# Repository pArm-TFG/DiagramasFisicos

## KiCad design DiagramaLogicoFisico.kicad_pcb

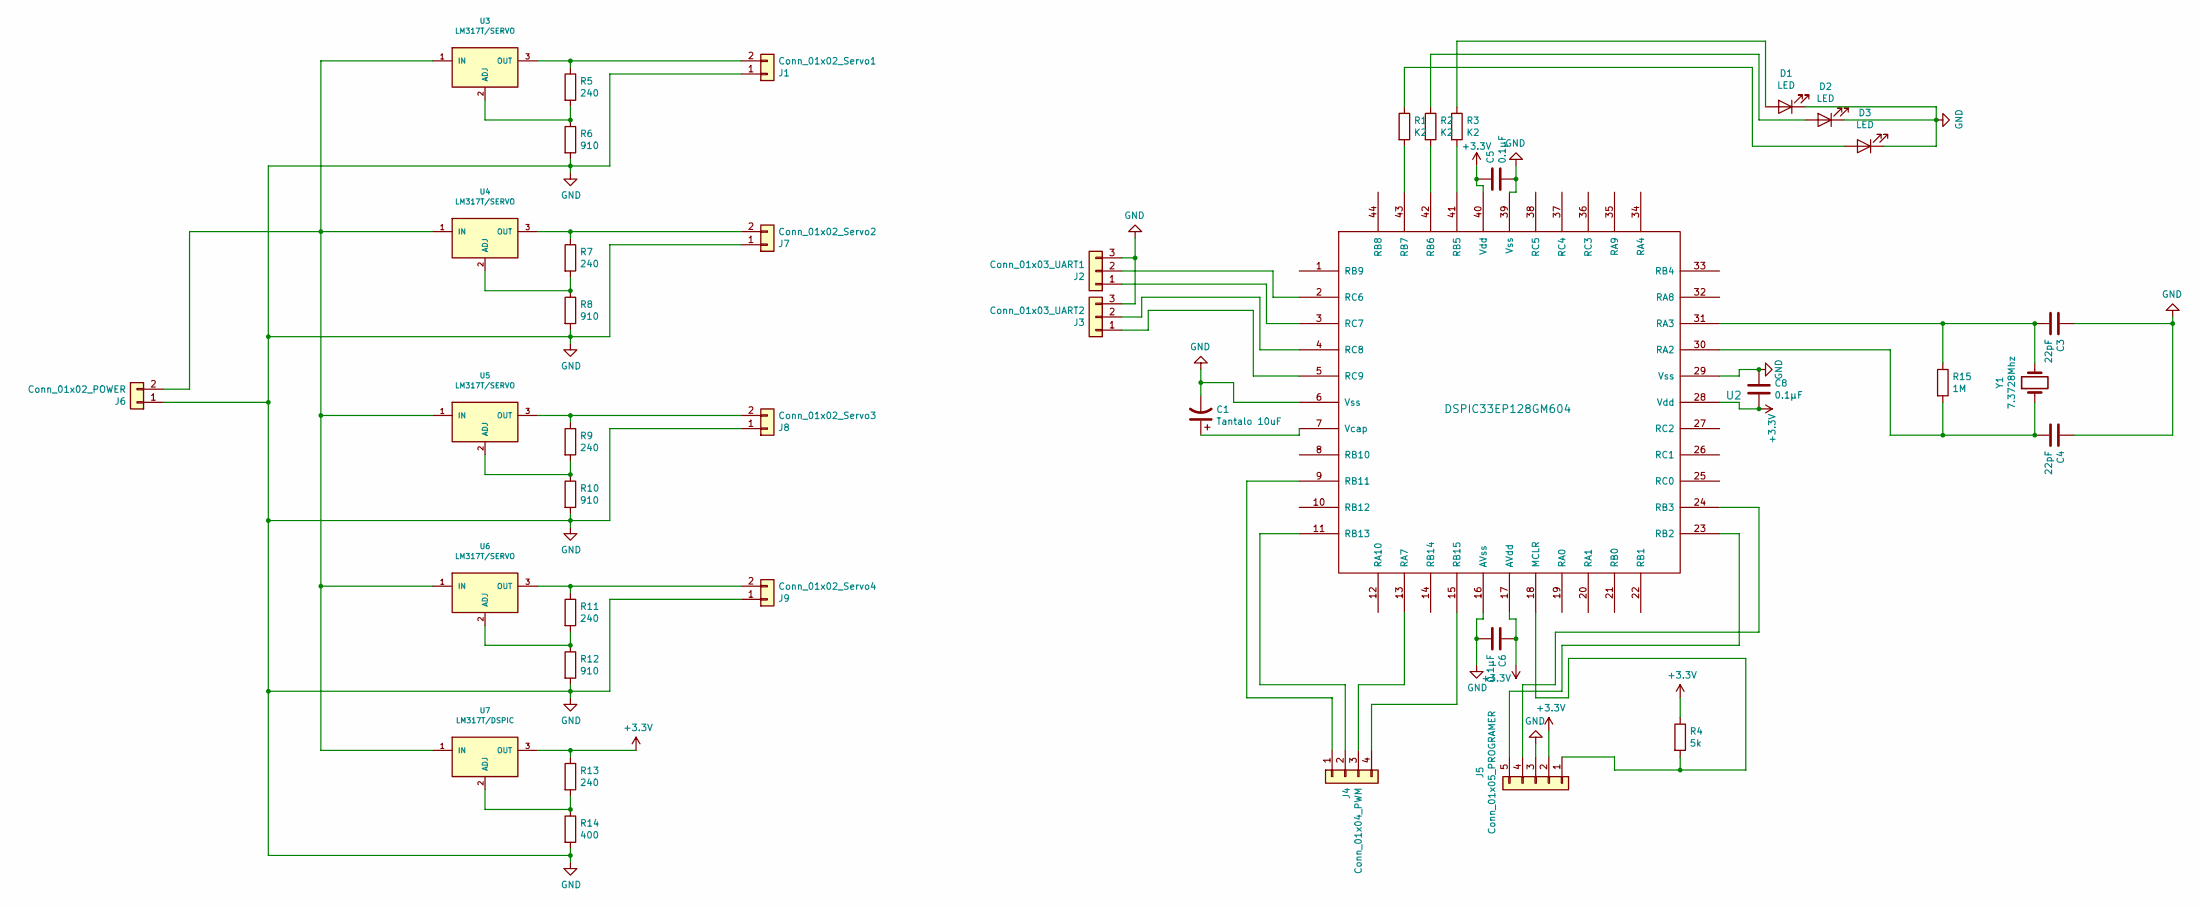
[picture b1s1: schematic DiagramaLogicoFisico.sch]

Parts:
C1: Tantalo 10uF; C_Disc_D3.8mm_W2.6mm_P2.50mm
C3, C4: 22pF; C_Disc_D3.8mm_W2.6mm_P2.50mm
C5, C6, C8: 0.1µF; C_Disc_D3.8mm_W2.6mm_P2.50mm
D1, D2, D3: LED; LED_D3.0mm
J1: Conn_01x02_Servo1; TerminalBlock_bornier-2_P5.08mm
J2: Conn_01x03_UART1; PinHeader_1x03_P2.54mm_Vertical
J3: Conn_01x03_UART2; PinHeader_1x03_P2.54mm_Vertical
J4: Conn_01x04_PWM; PinHeader_1x04_P2.54mm_Vertical
J5: Conn_01x05_PROGRAMER; PinHeader_1x05_P2.54mm_Vertical
J6: Conn_01x02_POWER; TerminalBlock_bornier-2_P5.08mm
J7: Conn_01x02_Servo2; TerminalBlock_bornier-2_P5.08mm
J8: Conn_01x02_Servo3; TerminalBlock_bornier-2_P5.08mm
J9: Conn_01x02_Servo4; TerminalBlock_bornier-2_P5.08mm
R1, R2, R3: K2; R_Axial_DIN0204_L3.6mm_D1.6mm_P5.08mm_Horizontal
R4: 5k; R_Axial_DIN0204_L3.6mm_D1.6mm_P5.08mm_Horizontal
R5, R7, R9, R11, R13: 240; R_Axial_DIN0204_L3.6mm_D1.6mm_P5.08mm_Horizontal
R6, R8, R10, R12: 910; R_Axial_DIN0204_L3.6mm_D1.6mm_P5.08mm_Horizontal
R14: 400; R_Axial_DIN0204_L3.6mm_D1.6mm_P5.08mm_Horizontal
R15: 1M; R_Axial_DIN0204_L3.6mm_D1.6mm_P5.08mm_Horizontal
U2: DSPIC33EP128GM604; TQFP-44_10x10mm_P0.8mm
U3, U4, U5, U6: LM317T/SERVO; TO-220-3_Vertical
U7: LM317T/DSPIC; TO-220-3_Vertical
Y1: 7.3728Mhz; Crystal_HC18-U_Vertical

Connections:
+3V3: C5.1, C6.1, C8.2, J5.2, R4.1, R13.1, U2.17 (AVdd), U2.28 (Vdd), U2.40 (Vdd), U7.3 (OUT)
GND: C1.2, C3.1, C4.1, C5.2, C6.2, C8.1, D1.1 (K), D2.1 (K), D3.1 (K), J1.1, J2.3, J3.3, J5.3, J6.1, J7.1, J8.1, J9.1, R6.2, R8.2, R10.2, R12.2, R14.2, U2.6 (Vss), U2.16 (AVss), U2.29 (Vss), U2.39 (Vss)
unnamed: C1.1, U2.7 (Vcap)
unnamed: C3.2, R15.1, U2.31 (RA3), Y1.2
unnamed: C4.2, R15.2, U2.30 (RA2), Y1.1
unnamed: D1.2 (A), R3.1
unnamed: D2.2 (A), R2.1
unnamed: D3.2 (A), R1.1
unnamed: J1.2, R5.1, U3.3 (OUT)
unnamed: J2.1, U2.3 (RC7)
unnamed: J2.2, U2.2 (RC6)
unnamed: J3.1, U2.5 (RC9)
unnamed: J3.2, U2.4 (RC8)
unnamed: J4.1, U2.9 (RB11)
unnamed: J4.2, U2.11 (RB13)
unnamed: J4.3, U2.13 (RA7)
unnamed: J4.4, U2.15 (RB15)
unnamed: J5.1, R4.2, U2.18 (MCLR)
unnamed: J5.4, U2.24 (RB3)
unnamed: J5.5, U2.23 (RB2)
unnamed: J6.2, U3.1 (IN), U4.1 (IN), U5.1 (IN), U6.1 (IN), U7.1 (IN)
unnamed: J7.2, R7.1, U4.3 (OUT)
unnamed: J8.2, R9.1, U5.3 (OUT)
unnamed: J9.2, R11.1, U6.3 (OUT)
unnamed: R1.2, U2.43 (RB7)
unnamed: R2.2, U2.42 (RB6)
unnamed: R3.2, U2.41 (RB5)
unnamed: R5.2, R6.1, U3.2 (ADJ)
unnamed: R7.2, R8.1, U4.2 (ADJ)
unnamed: R9.2, R10.1, U5.2 (ADJ)
unnamed: R11.2, R12.1, U6.2 (ADJ)
unnamed: R13.2, R14.1, U7.2 (ADJ)

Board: 2 copper layers, 40 parts (0 on the bottom side), 32 nets, no tracks yet.

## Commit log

2020-02-18 Changes to directory tree. Changed names from Spanish to English
2020-02-19 Updated KiCad.Updated componenents and libraries.
2020-02-19 Added subcircuits. Voltage regulator and crystal oscilator
2020-02-21 Added PWM's, UART's, LED's and Probe conections.
2020-02-29 Added new a new DSP footprint to the diagram
2020-03-17 Added extra PWM and fixed pin 15, added new footprints
2020-03-21 Añadidos condensadores a pines de alimentación
2020-03-24 Añadidos condensadores a pines de alimentación y establecido el circuito MCLR
2020-03-25 Añadido el circuito de alimentación de motores y MCU, en principio se ha terminado el circuito lógico
2020-03-31 Arreglados diversos errores tras la revisión de Norberto y finalizado el circuito lógico
2020-03-31 Arreglados diversos errores tras la revisión de Norberto y finalizado el circuito lógico, añadidas etiquetas a cada componente
2020-04-05 Proyecto Almost Released
2020-04-16 Proyecto Almost Released Vias
2020-04-21 Proyecto Almost Released Fixed
2020-05-09 Proyecto Almost finalizado
2020-05-19 Añadido puerto tris y clema extra
2020-06-01 Añadido los circuitos de interruptores y sus pines de alimentación
2020-06-02 Revisada la posición del cristal y engrosadas algunas pistas
2020-06-06 Pasadas comprobaciones de HW y modificaciones con respecto a la sonda
2020-06-07 Aumentado el espacio para la sonda
2020-07-01 añadidas algunas modifiaciones
2020-07-07 Sustituido el regulador del dspic
2020-07-07 Corregidos los valores de resistencias de los LM317 y alejado el regulador del dspic
2020-07-07 Añadidas las mascaras finales de impresión
2020-07-21 Arreglados los LM317
2020-10-06 Updated Physical diagram
